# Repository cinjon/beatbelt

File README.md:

BeatBelt was a board that Ivan and I built in March 2013. We completed Rev1 and had five boards made.

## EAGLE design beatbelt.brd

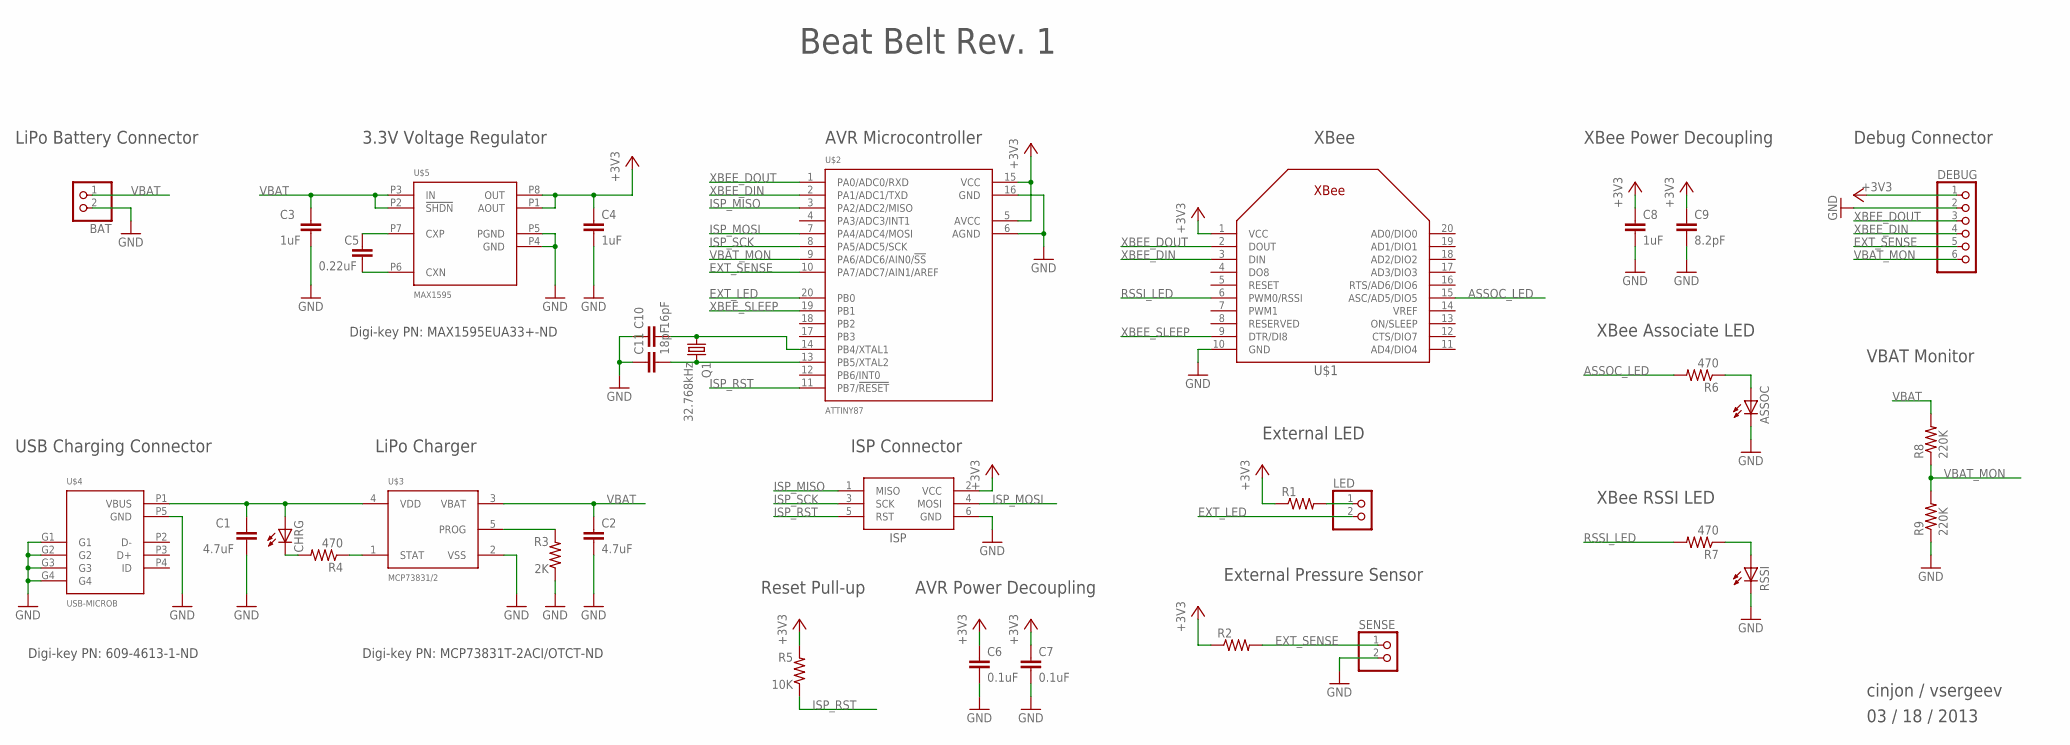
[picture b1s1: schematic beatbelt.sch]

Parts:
ASSOC: LEDCHIPLED_0805; CHIPLED_0805
BAT: JST_2PIN-SMT-RA; JST-PH-2-SMT-RA
C1, C2: 4.7uF; C0805
C3, C4, C8: 1uF; C0805
C5: 0.22uF; C0603
C6, C7: 0.1uF; C0805
C9: 8.2pF; C0805
C10: 16pF; C0603
C11: 18pF; C0603
CHRG: LEDCHIPLED_0805; CHIPLED_0805
DEBUG: PINHD-1X6; 1X06
ISP: AVRISP-6; AVRISP
LED: PINHD-1X2; 1X02
Q1: 32.768kHz; TC26V
R1, R2: R-US_R0805; R0805
R3: 2K; R0805
R4, R6, R7: 470; R0805
R5: 10K; R0805
R8, R9: 220K; R0805
RSSI: LEDCHIPLED_0805; CHIPLED_0805
SENSE: PINHD-1X2; 1X02
U$1: XBEE
U$2: ATTINY87; SOIC20S
U$3: MCP73831/2; SOT23-5L
U$4: USB-MICROB
U$5: MAX1595; UMAX8

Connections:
+3V3: C4.1, C6.1, C7.1, C8.1, C9.1, DEBUG.1, ISP.2 (VCC), R1.1, R2.1, R5.2, U$1.1 (VCC), U$2.5 (AVCC), U$2.15 (VCC), U$5.P1 (AOUT), U$5.P8 (OUT)
ASSOC_LED: R6.2, U$1.15 (ASC/AD5/DIO5)
EXT_LED: LED.2, U$2.20 (PB0)
EXT_SENSE: DEBUG.5, R2.2, SENSE.1, U$2.10 (PA7/ADC7/AIN1/AREF)
GND: ASSOC.C, BAT.2 (1), C1.2, C2.2, C3.2, C4.2, C6.2, C7.2, C8.2, C9.2, C10.1, C11.1, DEBUG.2, ISP.6 (GND), R3.1, R9.1, RSSI.C, SENSE.2, U$1.10 (GND), U$2.6 (AGND), U$2.16 (GND), U$3.2 (VSS), U$4.G1, U$4.G2, U$4.G3, U$4.G4, U$4.P5 (GND), U$5.P4 (GND), U$5.P5 (PGND)
ISP_MISO: ISP.1 (MISO), U$2.3 (PA2/ADC2/MISO)
ISP_MOSI: ISP.4 (MOSI), U$2.7 (PA4/ADC4/MOSI)
ISP_RST: ISP.5 (RST), R5.1, U$2.11 (PB7/!RESET)
ISP_SCK: ISP.3 (SCK), U$2.8 (PA5/ADC5/SCK)
unnamed: CHRG.C, R4.2
unnamed: LED.1, R1.2
unnamed: R3.2, U$3.5 (PROG)
unnamed: R4.1, U$3.1 (STAT)
unnamed: C1.1, CHRG.A, U$3.4 (VDD), U$4.P1 (VBUS)
unnamed: ASSOC.A, R6.1
unnamed: C5.1, U$5.P7 (CXP)
unnamed: C5.2, U$5.P6 (CXN)
unnamed: R7.1, RSSI.A
unnamed: C10.2, Q1.1, U$2.14 (PB4/XTAL1)
unnamed: C11.2, Q1.2, U$2.13 (PB5/XTAL2)
RSSI_LED: R7.2, U$1.6 (PWM0/RSSI)
VBAT: BAT.1 (2), C2.1, C3.1, R8.2, U$3.3 (VBAT), U$5.P2 (!SHDN), U$5.P3 (IN)
VBAT_MON: DEBUG.6, R8.1, R9.2, U$2.9 (PA6/ADC6/AIN0/!SS)
XBEE_DIN: DEBUG.4, U$1.3 (DIN), U$2.2 (PA1/ADC1/TXD)
XBEE_DOUT: DEBUG.3, U$1.2 (DOUT), U$2.1 (PA0/ADC0/RXD)
XBEE_SLEEP: U$1.9 (DTR/DI8), U$2.19 (PB1)

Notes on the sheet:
External LED
External Pressure Sensor
XBee
LiPo Battery Connector
Beat Belt Rev. 1
AVR Microcontroller
ISP Connector
LiPo Charger
3.3V Voltage Regulator
AVR Power Decoupling
USB Charging Connector
Digi-key PN: 609-4613-1-ND
Digi-key PN: MCP73831T-2ACI/OTCT-ND
Digi-key PN: MAX1595EUA33+-ND
Reset Pull-up
XBee Power Decoupling
XBee Associate LED
XBee RSSI LED
Debug Connector
VBAT Monitor
cinjon / vsergeev
03 / 18 / 2013

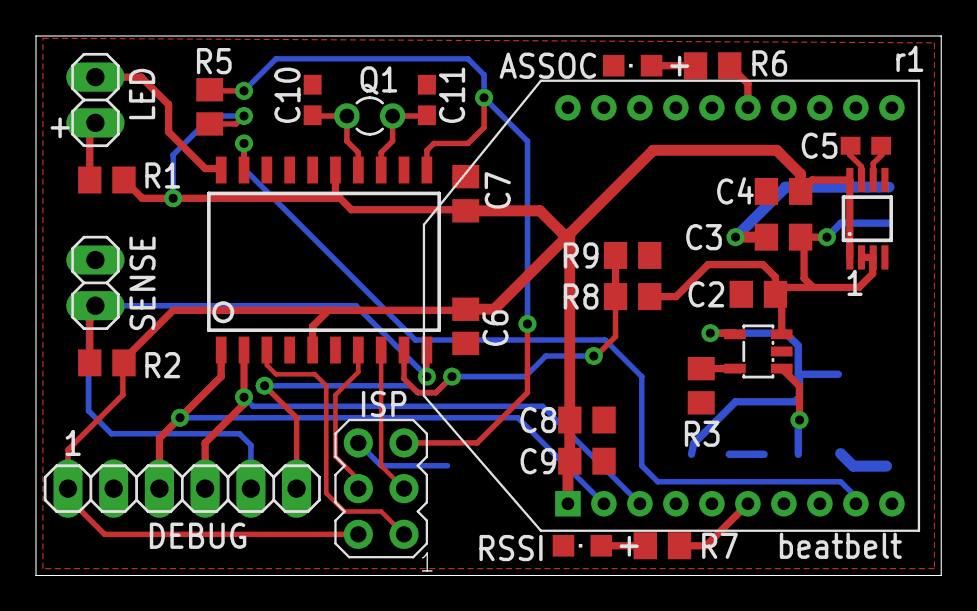
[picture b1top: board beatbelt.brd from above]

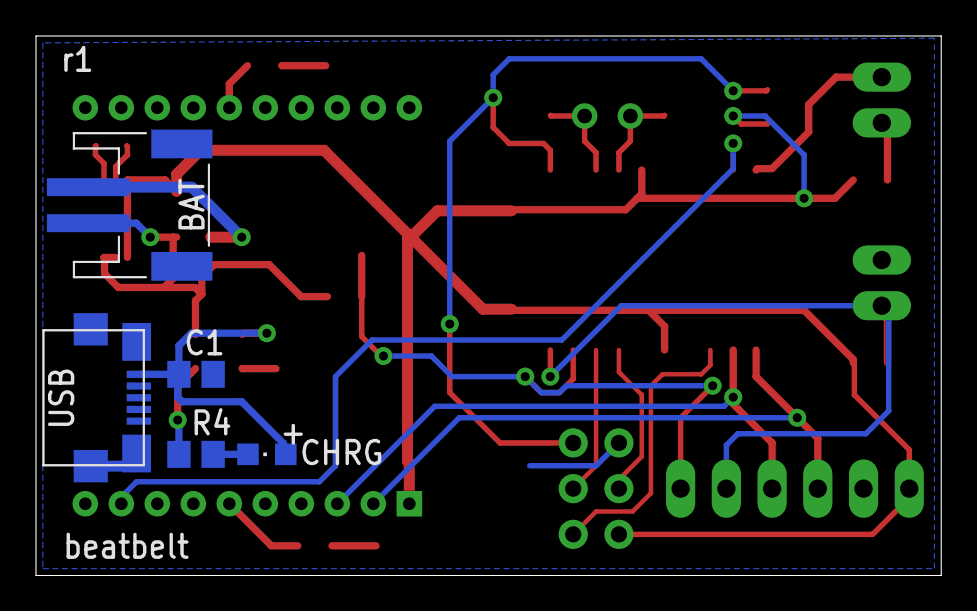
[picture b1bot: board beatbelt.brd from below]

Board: 2 copper layers, 50.3 x 30.0 mm, 34 parts (5 on the bottom side), 26 nets.

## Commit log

2013-11-18 to github
